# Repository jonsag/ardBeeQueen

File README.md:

# ardBeeQueen
A simple project to control a bee queen breeding chamber

Parts needed
===============
1 x Arduino Pro Mini, kjell.com art#87964  
1 x Arduino USB to Serial Converter, kjell.com art#87872  
2 x Arduino Single Relay Module, kjell.com art#87878  
1 x LCD Display, kjell.com art#90215  
1 x Dallas 1-wire Temp and Humidity Sensor DHT11, kjell.com art#87877 or  
1 x Dallas 1-wire Temp and Humidity Sensor DHT22, kjell.com art#90647  
1 x Rotary encoder, kjell.com art#87918  
1 x 10kohm Potentiometer, kjell.com art#90633  
1 x 220ohm resistor  
1 x 10K ohm resistor  
2 x 0,47uF capacitor  

Casing to hold everything

Wires and soldering material  

If you want to build a PCB using the Gerber file you will also need some headers and connnectors.  

Building electrical  
===============
Use schemes ardBeeQueenFritz* or Schematic_ardBeeQueen-v2_ardBeeQueen-v2_* to build.  
If you do not use the encoder you must still pull up D7 with a 10K resistor to VCC.  

Eagle PCB  
===============
If using the 50x52 PCB in Documents/Eagle directory, you can mount it in box electrokit.com, art#12109003  
Outside measures: 69 x 102 x 37 mm  
Inside measures: 63 x 96 x 33 mm  

If using the 105x84 PCB in Documents/Eagle directory, you can mount it in box electrokit.com, art#12109005  
Outside measures: 103 x 148 x 56 mm  
Insode measures: 96 x 142 x 52 mm  

Note
===============
All commands in the following instructions are run on Linux  
All links are valid and versions are the latest as of february 2019  

Set up Arduino IDE
===============
Go to https://www.arduino.cc/en/main/software and download Arduino IDE for your architecture and system  
>$ wget https://downloads.arduino.cc/arduino-1.8.10-linux64.tar.xz  
>$ tar xvJf arduino-1.8.10-linux64.tar.xz -C ~/bin/  
>$ ln -s arduino-1.8.10/arduino ~/bin/arduino  

Get libraries 
---------------

Adafruit Unified Sensor library  
---------------
Download library from https://www.arduinolibraries.info/libraries/adafruit-unified-sensor  
>$ wget http://downloads.arduino.cc/libraries/github.com/adafruit/Adafruit_Unified_Sensor-1.0.3.zip  
>$ unzip Adafruit_Unified_Sensor-1.0.3.zip -d ~/bin/arduino-1.8.10/libraries/  
>$ mv ~/bin/arduino-1.8.10/libraries/Adafruit_Unified_Sensor-1.0.3 ~/bin/arduino-1.8.10/libraries/Adafruit_Unified_Sensor  

DHT sensor library  
---------------
Download library from https://www.arduinolibraries.info/libraries/dht-sensor-library  
>$ wget http://downloads.arduino.cc/libraries/github.com/adafruit/DHT_sensor_library-1.3.7.zip  
>$ unzip DHT_sensor_library-1.3.7.zip -d ~/bin/arduino-1.8.10/libraries/  
>$ mv ~/bin/arduino-1.8.10/libraries/DHT_sensor_library-1.3.7 ~/bin/arduino-1.8.10/libraries/DHT_sensor_library  

Programming the Arduino Mini Pro
===============

If using the Arduino USB 2 Serial  
--------------------
Connect the programmer to your Pro Mini  
GND/BLK -> GND  
+5V -> VCC  
TX -> RX  
RX -> TX  
EXT RESET -> GRN

Open your sketch in Arduino IDE  
Select 'Tools'->'Port'  
* /dev/ttyACM0 or  
* /dev/ttyUSB0  

Select 'Tools'->'Board'  
For the 3.3V versions of the Arduino Pro Mini, select:  
* Arduino Pro or  
* Pro Mini (3.3V, 8 MHz) w/ ATmega328P or  
* Arduino Pro or  
* Pro Mini (3.3V, 8 MHz) w/ ATmega168  
(depending on the microcontroller on your board)  
For the 5V versions of the Arduino Pro Mini, select  
* Arduino Duemilanove or  
* Nano w/ ATmega328P or  
* Arduino Diecimila, Duemilanove (this is what I used) or  
* Nano w/ ATmega168

If using the PC-PL2303 Cable  
---------------
Black cable -> GND  
Green cable -> TXD  
White cable -> RXD  
Red cable -> VCC (5V)  

You will have to press the reset button on the arduino to reset it right before the upload from Arduino IDE.  

Fritzing  
===============
Download fritzing at http://fritzing.org/download/  

>$ wget http://fritzing.org/download/0.9.3b/linux-64bit/fritzing-0.9.3b.linux.AMD64.tar.bz2  
>$ tar jxvf ~/Downloads/fritzing-0.9.3b.linux.AMD64.tar.bz2 -C ~/bin/  
>$ ln -s fritzing-0.9.3b.linux.AMD64/Fritzing ~/bin/fritzing  

EasyEDA  
==============
Use easyEDA online at https://easyeda.com/editor or download client from https://easyeda.com/page/download  

>$ wget https://image.easyeda.com/files/easyeda-client-linux-x64.zip  
>$ unzip easyeda-client-linux-x64.zip  
>$ cd easyeda-client-linux-x64  
>$ sudo bash install.sh  

Download local router from https://docs.easyeda.com/en/PCB/Route/index.html#Local-Auto-Router  
>$ wget https://image.easyeda.com/files/EasyEDA-Router-v0.8.1.zip  
>$ unzip EasyEDA-Router-v0.8.1.zip  
>$ cd EasyEDA-Router-v0.8.1  

Start router with  
>$ bash lin64.sh  

Autodesk EAGLE
===================
Download EAGLE at https://www.autodesk.com/products/eagle/free-download  

>$ tar xvzf Autodesk_EAGLE_9.3.1_English_Linux_64bit.tar.gz -C ~/bin  
>$ ln -s eagle-9.3.1/eagle ~/bin/eagle  

Start and sign in with your Autodesk account

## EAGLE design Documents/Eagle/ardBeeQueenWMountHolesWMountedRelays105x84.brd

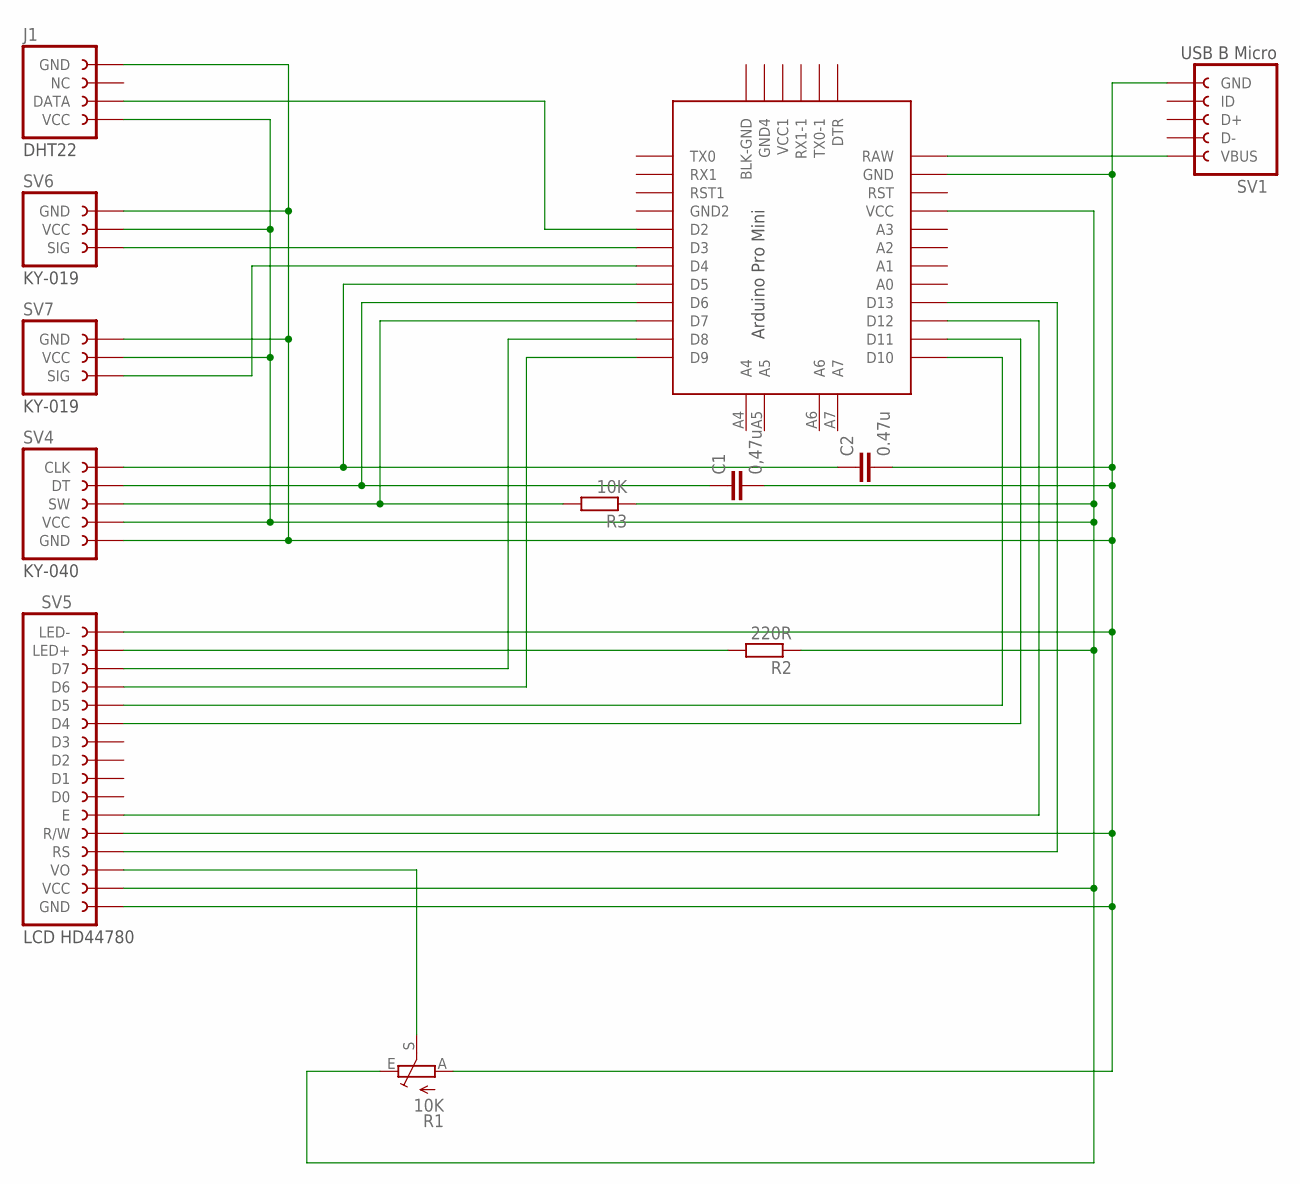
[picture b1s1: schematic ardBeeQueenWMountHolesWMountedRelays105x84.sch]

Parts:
C1: 0,47u; C050-024X044
C2: 0.47u; C050-024X044
J1: DHT22_4-PIN_FEMALE_HEADERPTH; DHT22_4-PIN_FEMALE_HEADER
R1: 10K; B25P
R2: 220R; 0207/10
R3: 10K; 0207/10
SV1: MICROUSB_B_BREAKOUT_5-PIN_FEMALE_HEADERWITH_MOUNT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; MICROUSB_B_BREAKOUT_5-PIN_FEMALE_HEADER_W_MOUNT_HOLES
SV4: KY-040_5-PIN_FEMALE_HEADER
SV5: LCD-HD44780-16-PIN_FEMALE_HEADER
SV6, SV7: KY-019_3-PIN_FEMALE_HEADERANGLED_W_MOUNT_HOLES; KY-019_3-PIN_FEMALE_HEADER_ANGLED_W_MOUNT_HOLES
U$1: ARDUINO_PRO_MINI-2

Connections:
unnamed: R1.S, SV5.VO
unnamed: R2.2, SV5.LED+
unnamed: SV5.D6, U$1.D9
unnamed: SV5.D7, U$1.D8
unnamed: SV5.D5, U$1.D10
unnamed: SV5.D4, U$1.D11
unnamed: SV5.E, U$1.D12
unnamed: SV5.RS, U$1.D13
unnamed: R3.2, SV4.SW, U$1.D7
unnamed: C1.1, SV4.DT, U$1.D6
unnamed: C2.1, SV4.CLK, U$1.D5
unnamed: J1.DATA, U$1.D2
unnamed: SV6.SIG, U$1.D3
unnamed: SV7.SIG, U$1.D4
unnamed: J1.VCC, R1.E, R2.1, R3.1, SV4.VCC, SV5.VCC, SV6.VCC, SV7.VCC, U$1.VCC
unnamed: C1.2, C2.2, J1.GND, R1.A, SV1.GND, SV4.GND, SV5.GND, SV5.LED-, SV5.R/W, SV6.GND, SV7.GND, U$1.GND
unnamed: SV1.VBUS, U$1.RAW

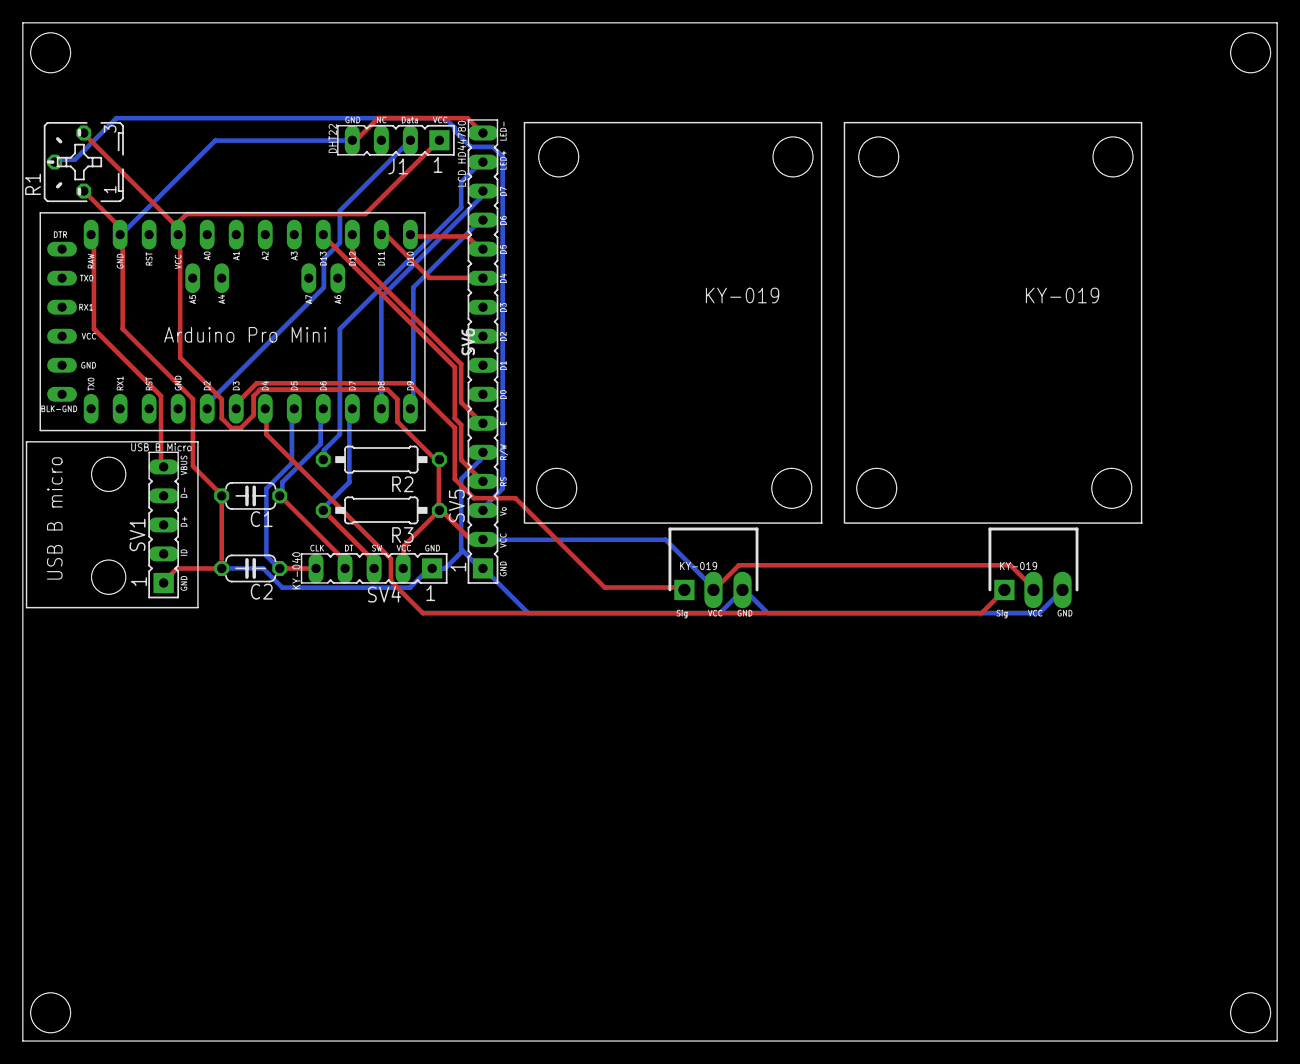
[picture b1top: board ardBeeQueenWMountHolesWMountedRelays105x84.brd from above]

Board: 2 copper layers, 109.8 x 89.1 mm, 12 parts (0 on the bottom side), 17 nets.

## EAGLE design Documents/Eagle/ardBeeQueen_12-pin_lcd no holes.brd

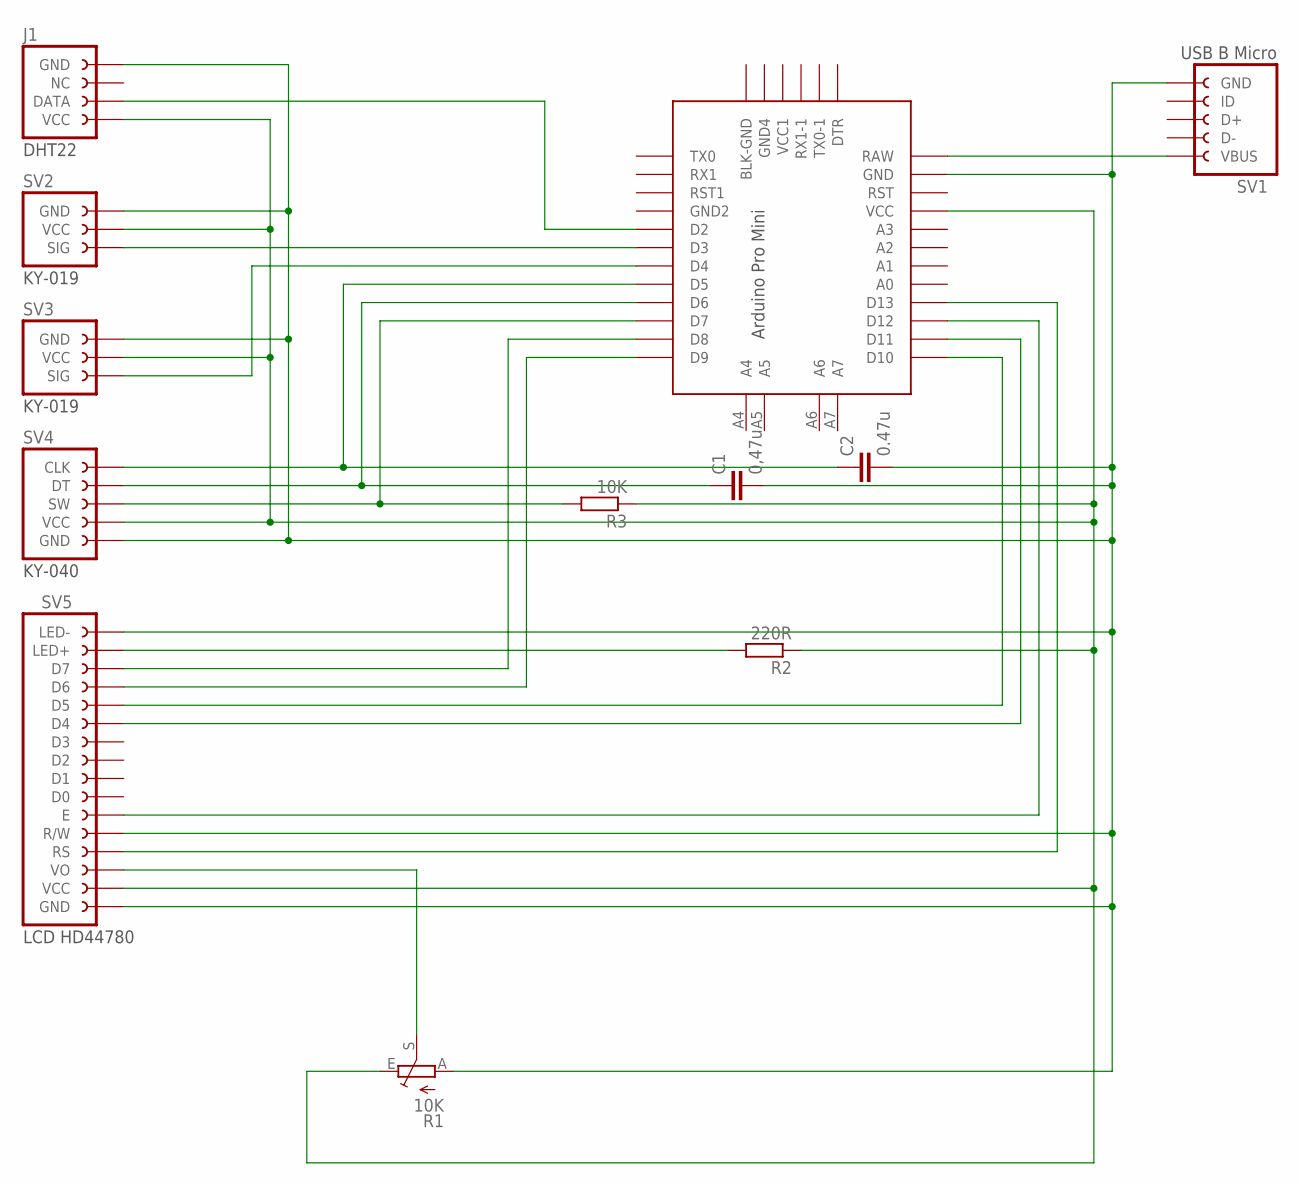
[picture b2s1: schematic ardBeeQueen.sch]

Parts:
C1: 0,47u; C050-024X044
C2: 0.47u; C050-024X044
J1: DHT22_4-PIN_FEMALE_HEADERPTH; DHT22_4-PIN_FEMALE_HEADER
R1: 10K; B25P
R2: 220R; 0207/10
R3: 10K; 0207/10
SV1: MICROUSB_B_BREAKOUT_5-PIN_FEMALE_HEADERWITH_MOUNT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; MICROUSB_B_BREAKOUT_5-PIN_FEMALE_HEADER_W_MOUNT_HOLES
SV2, SV3: KY-019_3-PIN_FEMALE_HEADER
SV4: KY-040_5-PIN_FEMALE_HEADER
SV5: LCD-HD44780-16-PIN_FEMALE_HEADER
U$1: ARDUINO_PRO_MINI-2

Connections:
unnamed 0: R1.S, SV5.VO; also elsewhere on the board
unnamed 1: R2.2, SV5.LED+; also elsewhere on the board
unnamed 2: SV5.D6, U$1.D9; also elsewhere on the board
unnamed 3: SV5.D7, U$1.D8; also elsewhere on the board
unnamed 4: SV5.D5, U$1.D10; also elsewhere on the board
unnamed 5: SV5.D4, U$1.D11; also elsewhere on the board
unnamed 6: SV5.E, U$1.D12; also elsewhere on the board
unnamed 7: SV5.RS, U$1.D13; also elsewhere on the board
unnamed: R3.2, SV4.SW, U$1.D7
unnamed: C1.1, SV4.DT, U$1.D6
unnamed: C2.1, SV4.CLK, U$1.D5
unnamed: J1.DATA, U$1.D2
unnamed: SV2.SIG, U$1.D3
unnamed: SV3.SIG, U$1.D4
unnamed 14: J1.VCC, R1.E, R2.1, R3.1, SV2.VCC, SV3.VCC, SV4.VCC, SV5.VCC, U$1.VCC; also elsewhere on the board
unnamed 15: C1.2, C2.2, J1.GND, R1.A, SV1.GND, SV2.GND, SV3.GND, SV4.GND, SV5.GND, SV5.LED-, SV5.R/W, U$1.GND; also elsewhere on the board
unnamed: SV1.VBUS, U$1.RAW

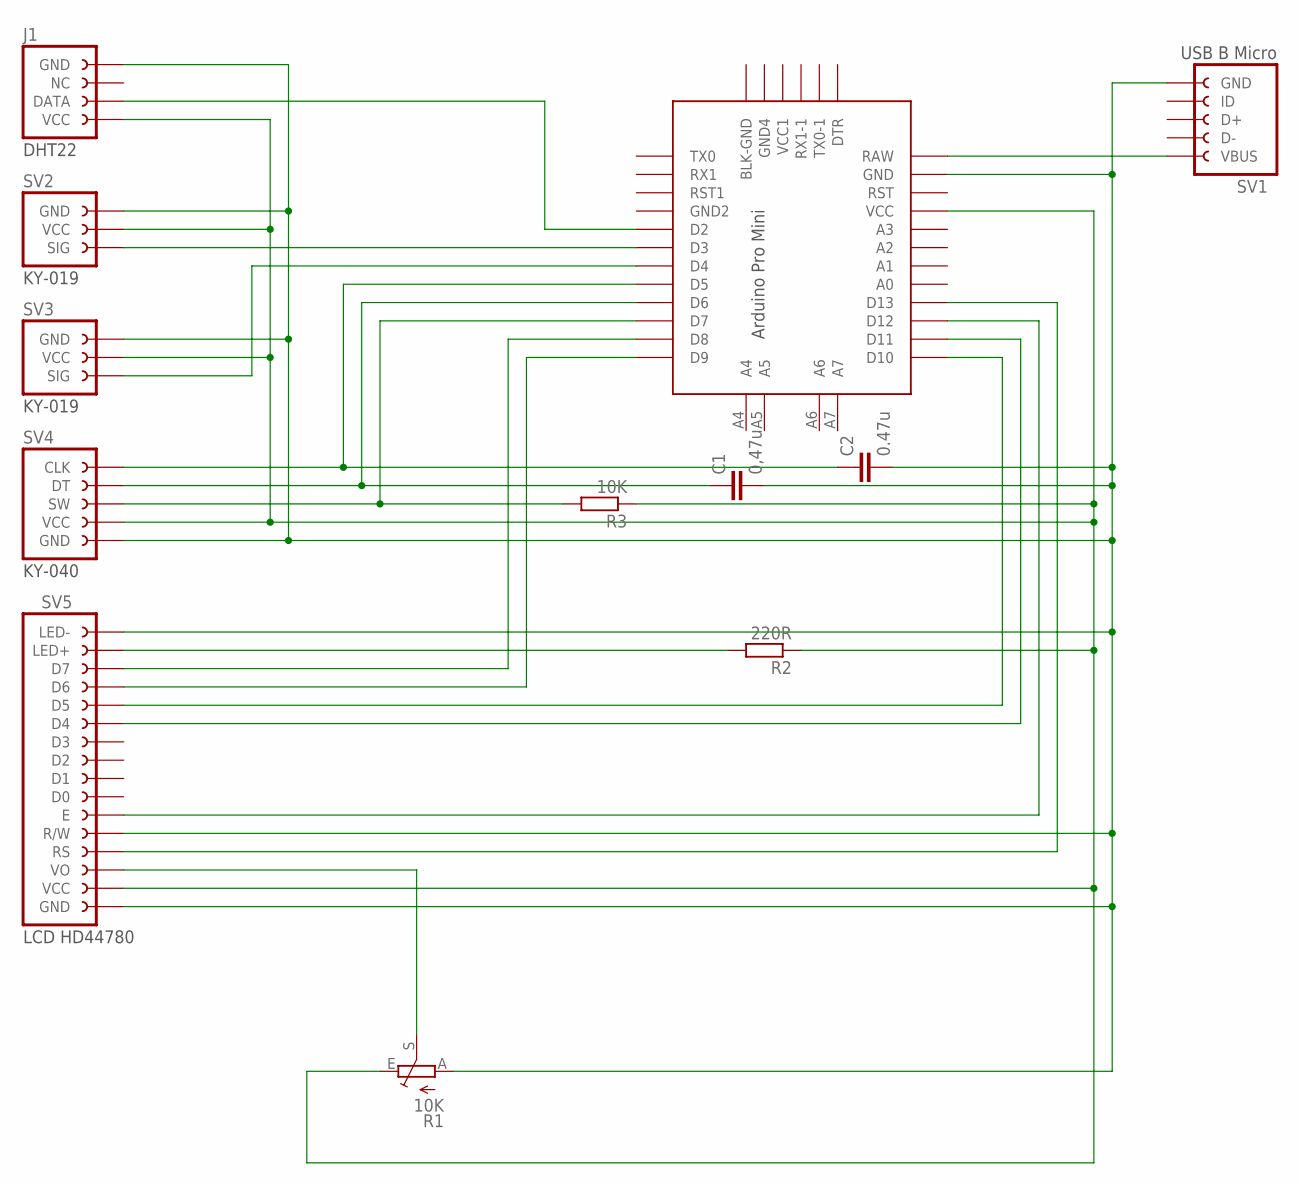
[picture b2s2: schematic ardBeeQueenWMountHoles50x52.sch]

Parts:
C1: 0,47u; C050-024X044
C2: 0.47u; C050-024X044
J1: DHT22_4-PIN_FEMALE_HEADERPTH; DHT22_4-PIN_FEMALE_HEADER
R1: 10K; B25P
R2: 220R; 0207/10
R3: 10K; 0207/10
SV1: MICROUSB_B_BREAKOUT_5-PIN_FEMALE_HEADERWITH_MOUNT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; MICROUSB_B_BREAKOUT_5-PIN_FEMALE_HEADER_W_MOUNT_HOLES
SV2, SV3: KY-019_3-PIN_FEMALE_HEADER
SV4: KY-040_5-PIN_FEMALE_HEADER
SV5: LCD-HD44780-16-PIN_FEMALE_HEADER
U$1: ARDUINO_PRO_MINI-2

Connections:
unnamed 0: R1.S, SV5.VO; also elsewhere on the board
unnamed 1: R2.2, SV5.LED+; also elsewhere on the board
unnamed 2: SV5.D6, U$1.D9; also elsewhere on the board
unnamed 3: SV5.D7, U$1.D8; also elsewhere on the board
unnamed 4: SV5.D5, U$1.D10; also elsewhere on the board
unnamed 5: SV5.D4, U$1.D11; also elsewhere on the board
unnamed 6: SV5.E, U$1.D12; also elsewhere on the board
unnamed 7: SV5.RS, U$1.D13; also elsewhere on the board
unnamed: R3.2, SV4.SW, U$1.D7
unnamed: C1.1, SV4.DT, U$1.D6
unnamed: C2.1, SV4.CLK, U$1.D5
unnamed: J1.DATA, U$1.D2
unnamed: SV2.SIG, U$1.D3
unnamed: SV3.SIG, U$1.D4
unnamed 14: J1.VCC, R1.E, R2.1, R3.1, SV2.VCC, SV3.VCC, SV4.VCC, SV5.VCC, U$1.VCC; also elsewhere on the board
unnamed 15: C1.2, C2.2, J1.GND, R1.A, SV1.GND, SV2.GND, SV3.GND, SV4.GND, SV5.GND, SV5.LED-, SV5.R/W, U$1.GND; also elsewhere on the board
unnamed: SV1.VBUS, U$1.RAW

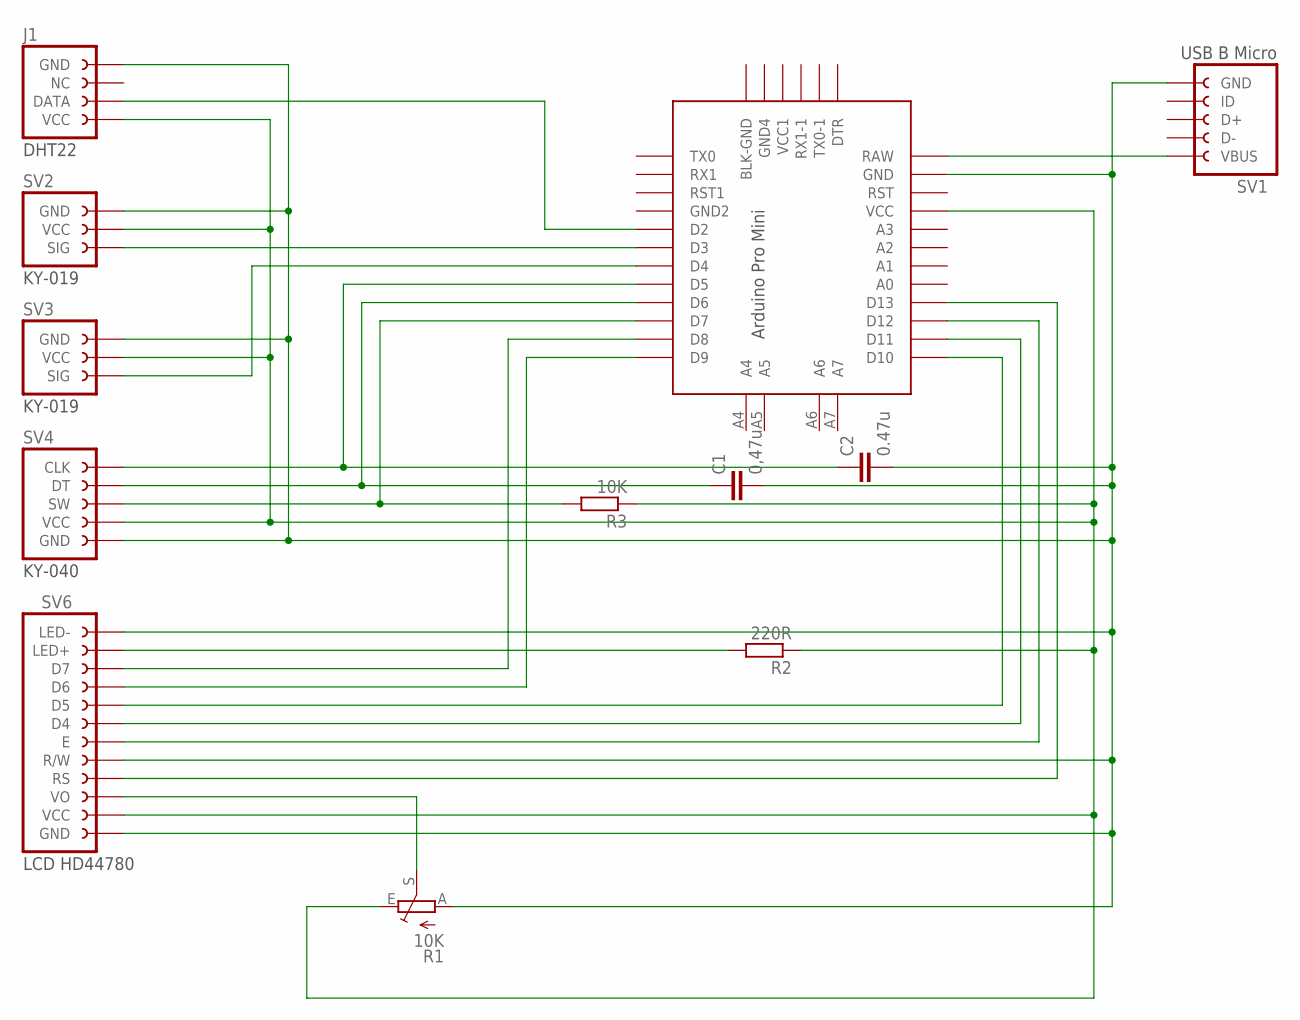
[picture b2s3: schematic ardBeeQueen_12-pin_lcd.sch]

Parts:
C1: 0,47u; C050-024X044
C2: 0.47u; C050-024X044
J1: DHT22_4-PIN_FEMALE_HEADERPTH; DHT22_4-PIN_FEMALE_HEADER
R1: 10K; B25P
R2: 220R; 0207/10
R3: 10K; 0207/10
SV1: MICROUSB_B_BREAKOUT_5-PIN_FEMALE_HEADERWITH_MOUNT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; MICROUSB_B_BREAKOUT_5-PIN_FEMALE_HEADER_W_MOUNT_HOLES
SV2, SV3: KY-019_3-PIN_FEMALE_HEADER
SV4: KY-040_5-PIN_FEMALE_HEADER
SV6: LCD-HD44780-12-PIN_FEMALE_HEADER
U$1: ARDUINO_PRO_MINI-2

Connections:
unnamed 0: R1.S, SV6.VO; also elsewhere on the board
unnamed 1: R2.2, SV6.LED+; also elsewhere on the board
unnamed 2: SV6.D6, U$1.D9; also elsewhere on the board
unnamed 3: SV6.D7, U$1.D8; also elsewhere on the board
unnamed 4: SV6.D5, U$1.D10; also elsewhere on the board
unnamed 5: SV6.D4, U$1.D11; also elsewhere on the board
unnamed 6: SV6.E, U$1.D12; also elsewhere on the board
unnamed 7: SV6.RS, U$1.D13; also elsewhere on the board
unnamed: R3.2, SV4.SW, U$1.D7
unnamed: C1.1, SV4.DT, U$1.D6
unnamed: C2.1, SV4.CLK, U$1.D5
unnamed: J1.DATA, U$1.D2
unnamed: SV2.SIG, U$1.D3
unnamed: SV3.SIG, U$1.D4
unnamed 14: J1.VCC, R1.E, R2.1, R3.1, SV2.VCC, SV3.VCC, SV4.VCC, SV6.VCC, U$1.VCC; also elsewhere on the board
unnamed 15: C1.2, C2.2, J1.GND, R1.A, SV1.GND, SV2.GND, SV3.GND, SV4.GND, SV6.GND, SV6.LED-, SV6.R/W, U$1.GND; also elsewhere on the board
unnamed: SV1.VBUS, U$1.RAW

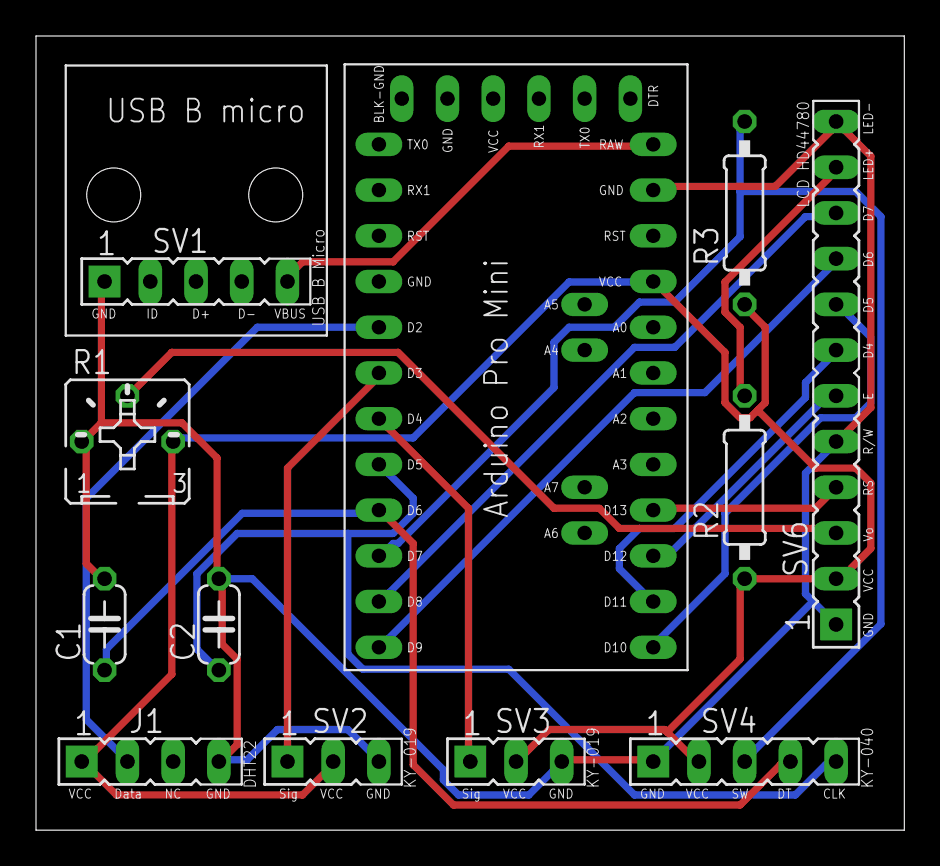
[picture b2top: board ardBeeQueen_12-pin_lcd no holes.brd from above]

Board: 2 copper layers, 48.2 x 44.1 mm, 12 parts (0 on the bottom side), 17 nets.

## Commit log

2018-05-15 Added fritz image
2018-05-16 Now has a DHT11. Measures humidity abd temperature, has LCD, has both heating and cooling relay.
2019-02-21 Reorganizing
2019-02-21 Changed to new DHT library
2019-02-23 Updated fritz and sketch
2019-02-24 Haf to add another sketch, as my Arduino Mini Pro is broken. D2 and D3 are shorted to each other, and D10 is not usable.
2019-02-24 Added rotary encoder to sketch
2019-02-24 Some renaming
2019-02-25 Added rotary encoder for changing set point
2019-02-25 Updated fritz with new components
2019-02-26 Near completion- Also added schematics and PCB
2019-02-26 Minor fixes
2019-02-26 Added to part list
2019-03-04 Documents
2019-03-04 delete
2019-03-05 Added board with mounted relays.# WARNING: head commit changed in the meantime
    delete
2019-03-10 updated eagle docs
2019-10-06 updated ino
2019-10-07 deleted files from Eagle
2019-10-11 added PID sketch
2019-10-12 added another PID ino
2019-10-12 PID output to LCD
2019-10-12 added plotting function and new ino
2019-10-12 improved plotting
2019-10-12 outputs windowTime and onTimeVal
2019-10-12 comments and some cleanup
2019-10-12 added eagle schematics and PCBs
2019-10-13 bug in PID3
2019-10-17 updated LCD config
2019-10-19 added air circulation fan
2019-10-19 redid the LCD outout, some more comments
2019-10-19 starting on autotune version
2019-10-19 renames
2019-10-19 mostly serial output changes
2019-10-20 comments and output changes
2019-10-20 straightening
2019-10-20 bugs
2019-10-20 shape ups
2019-10-20 many ...
2019-10-20 added PID4, mostly beautifying(!)
2019-10-20 deleted dew points and heat index from PIID3
2020-01-25 Eagle update
2021-01-26 schematic image
2022-05-29 moved to kicad
2025-01-26 new kicad version
